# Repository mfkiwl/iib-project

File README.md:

# Matt's 4th Year Project

## GPSDO
This contains the design files and firmware for a GPS disciplined oscillator. It combines the frequency reference from a Ublox MAX-M8Q GPS module with a low jitter timing reference to create a very stable and accurate user defined frequency reference. There are two identical buffered clock outputs as well as a 1Hz PPS. The PPS output is used as a timing reference for synchronizing the output streams of multiple independent SDRs. There is also a command line application to view the status of the GPS and PLL live.

## Amplifiers
This folder contains PCB designs for custom LNA's and PA's that make use of Minicircuits range of amplifier ICs.

## Lime-SDR
This folder contains various resources such as the modified gateware running on the Lime Mini's MAX10 FPGA, the design files for a small PCB to break the 0.1" header on the Lime Mini out to an SMA connector, and a setup guide.

## Model
This folder contains some python notebooks that attempt to model the RF system, in addition to a MATLAB program to compute the position of a source based on some time of flight measurements using a least squares approach.

## Software
This folder contains applications written in C++ that make use of the LimeSuite LMS API.

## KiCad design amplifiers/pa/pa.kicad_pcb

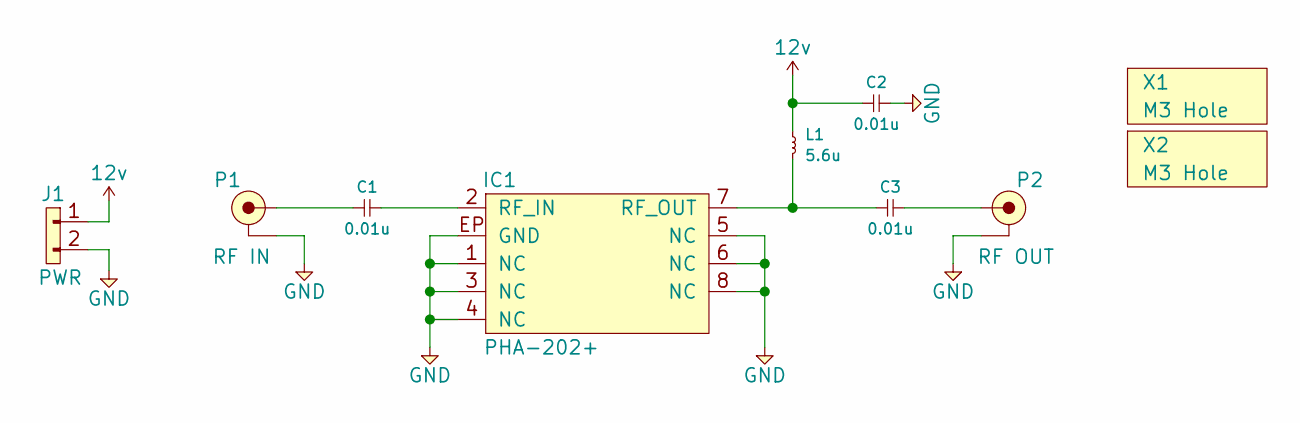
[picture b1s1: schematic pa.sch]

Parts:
C1, C2, C3: 0.01u; 0402; Mouser 80-C0402T103K4RACTU
IC1: PHA-202+; DL1636
J1: PWR; B02B-PASK
L1: 5.6u; WA8514-AE
P1: RF IN; SMA-EDGE; Farnell 1608592
P2: RF OUT; SMA-EDGE; Farnell 1608592
X1, X2: M3 Hole; M3_MOUNT

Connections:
12v: C2.1, J1.1, L1.1
GND: C2.2, IC1.1 (NC), IC1.3 (NC), IC1.4 (NC), IC1.5 (NC), IC1.6 (NC), IC1.8 (NC), IC1.EP (GND), J1.2, P1.2 (GND), P2.2 (GND)
unnamed: C1.1, P1.1 (RF)
unnamed: C1.2, IC1.2 (RF_IN)
unnamed: C3.1, IC1.7 (RF_OUT), L1.2
unnamed: C3.2, P2.1 (RF)

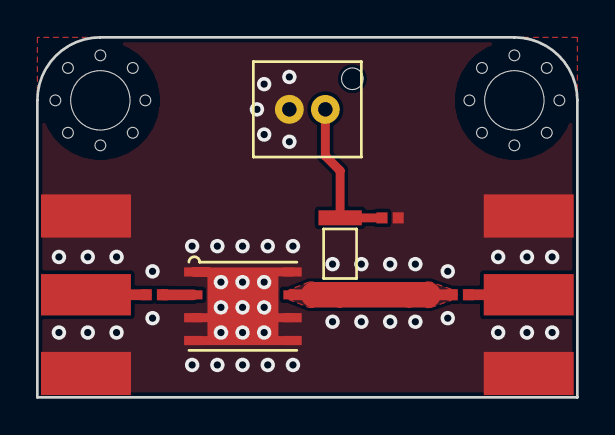
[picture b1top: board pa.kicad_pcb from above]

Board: 2 copper layers, 30.0 x 20.0 mm, 10 parts (0 on the bottom side), 6 nets.

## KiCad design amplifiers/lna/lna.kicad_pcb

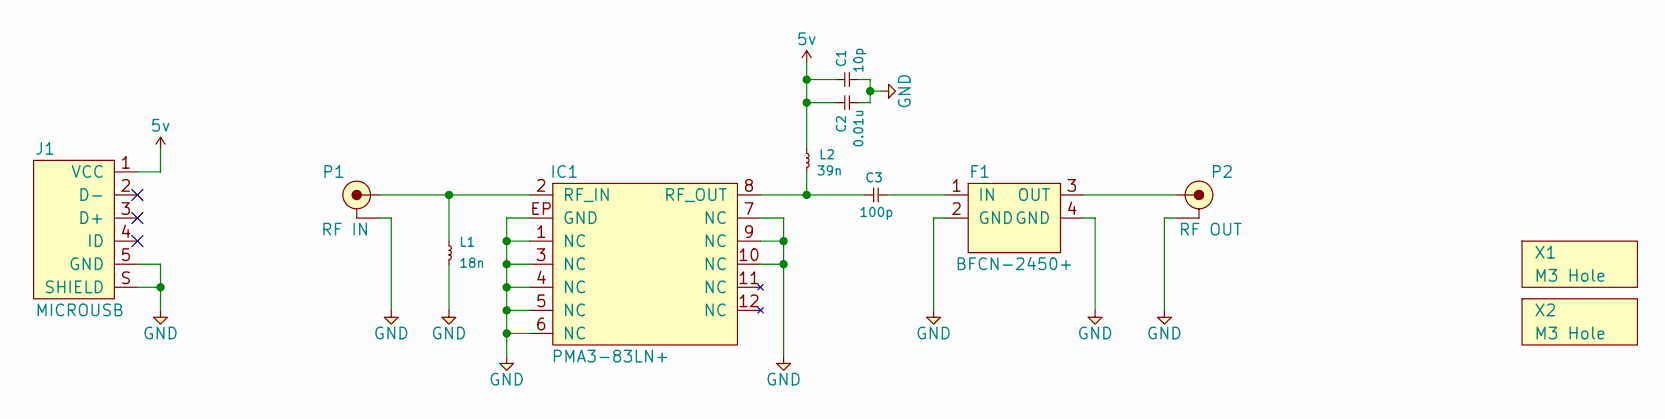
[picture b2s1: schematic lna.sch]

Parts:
C1: 10p; 0402; Mouser 80-C0402C100K5RACTU
C2: 0.01u; 0402; Mouser 80-C0402T103K4RACTU
C3: 100p; 0402; Mouser 581-0402YC101M
F1: BFCN-2450+; FV1206-4
IC1: PMA3-83LN+; DQ1225
J1: MICROUSB; MICROUSB_MOLEX_47589-0001; Farnell 1568023
L1: 18n; 0402; Mouser 81-LQG15HS18NJ02D
L2: 39n; 0402; Mouser 994-0402CS-39NXGLW
P1: RF IN; SMA-EDGE; Farnell 1608592
P2: RF OUT; SMA-EDGE; Farnell 1608592
X1, X2: M3 Hole; M3_MOUNT

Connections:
5v: C1.1, C2.1, J1.1 (VCC), L2.1
GND: C1.2, C2.2, F1.2 (GND), F1.4 (GND), IC1.1 (NC), IC1.3 (NC), IC1.4 (NC), IC1.5 (NC), IC1.6 (NC), IC1.7 (NC), IC1.9 (NC), IC1.10 (NC), IC1.EP (GND), J1.5 (GND), J1.S (SHIELD), L1.2, P1.2 (GND), P2.2 (GND)
unnamed: C3.1, IC1.8 (RF_OUT), L2.2
unnamed: C3.2, F1.1 (IN)
unnamed: F1.3 (OUT), P2.1 (RF)
unnamed: IC1.2 (RF_IN), L1.1, P1.1 (RF)

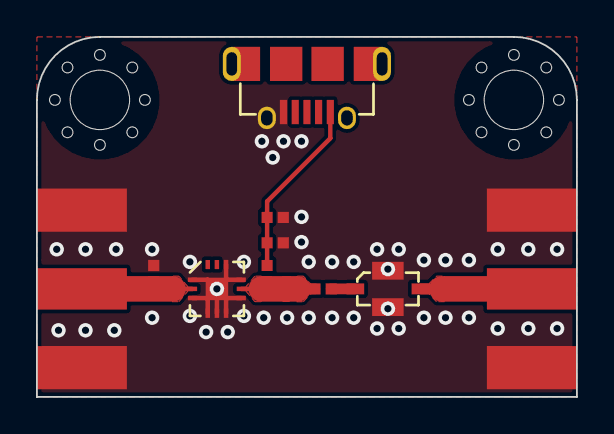
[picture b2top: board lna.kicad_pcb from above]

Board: 2 copper layers, 30.0 x 20.0 mm, 12 parts (0 on the bottom side), 6 nets.

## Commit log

2018-10-03 added pps_delta app and also some example data for meeting
2018-10-05 Modified GW to report exact sample of PPS sync
    Normally the counter only increments every two samples, so this fix doubles the accuracy of the PPS detection.
2018-10-08 added PPS analysis
2018-10-08 started system model
2018-10-09 added noise analysis
2018-10-10 started tdoa estimate
2018-10-10 changed to chans method for tdoa. started cross correlation in model
2018-10-11 tidied up notebooks
2018-10-11 added tof estimate
2018-10-12 tcvcxo investigation day
2018-10-15 Matlab TOF model started
2018-10-15 started on quantisation noise, need to do tests
2018-10-15 Added timing error and plotting
2018-10-15 wrote test script
2018-10-16 test data added
2018-10-17 finsihed system model with 1mhz chirp
2018-10-17 updated pps error analysis
2018-10-17 Added timing error to tof model
2018-10-18 Added error analysis to tof model
    Drift, and position dependent error added
2018-10-18 moved to 12 bit value
2018-10-18 Updated NIOS FW for 12 Bit DAC - 5311
2018-10-20 tuning algorithm seems to work
2018-10-20 added initial dac val
2018-10-20 Added 0 to 4095 range check on dac value
2018-10-20 changed initial value
2018-10-21 changed time
2018-10-21 holdover anaylsis done
2018-10-22 added system margin to model
2018-10-23 finalised noise model
2018-10-25 added 15mhz chirp
2018-10-25 slight change to spreadsheet
2018-10-26 started lna
2018-10-29 changed gain to db and frwq to 2.4g
2018-10-30 added custom waveform load and cross correlation in post
2018-10-31 moved to 15mhz chirp
2018-11-01 tidied up
2018-11-05 finsihed amplifier schematics
2018-11-05 finished pcbs
2018-11-05 generated gerbers
2018-11-20 tx-pps nolonger drops packets
2018-11-20 corrected cross correlation
2018-11-20 increased delay for mini pc
2018-11-20 rx software for bench test added
2018-11-20 removed print
2018-11-20 added inc file for rx
2018-11-21 tof over cable works
2018-11-21 delayed TX success
2018-11-21 added even/odd send for TX
2018-11-21 corrected offset printout
2018-11-21 success with two SDRs using single pulse gen
2018-11-21 test with independant gpsdos and SDRs successful
2018-11-21 increased ma length, looks good
2018-11-21 moved tuning to seperate function
2018-11-22 tuned tx ready to test
2018-11-22 test data
2018-11-22 added test 4 and 5
2018-12-16 sensitivity test done
2019-01-20 distance testing
2019-01-27 added rf loopback
2019-01-28 round trip timing testing
2019-02-10 round trip testing
2019-02-10 increased chirp length and tested max attenuation
2019-02-18 Revert "round trip testing"
    This reverts commit 17345d25075592627e6a63a8a3298749eaeb7350.
2019-02-18 reverted to 8 buffers TX
2019-02-18 moved software around and tidied up print outs
2019-02-18 increased DC corr window to 2^18
2019-02-18 added agc bypass
2019-02-19 enabled TxTSP and RxTSP
2019-02-19 enabled TxTSP and RxTSP and added cal enabled by default
2019-02-19 enabled TxTSP and RxTSP and added cal enabled by default and gain
2019-02-19 added tsp to round trip
2019-02-24 added search on xcor
2019-02-24 did test dry run
2019-02-28 field test data uploaded
2019-02-28 processed data for results
2019-03-15 field test round 2 data and results
